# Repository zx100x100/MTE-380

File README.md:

# MTE-380
Repo for all mechanical, electrical and software designs for our MTE-380 Robot

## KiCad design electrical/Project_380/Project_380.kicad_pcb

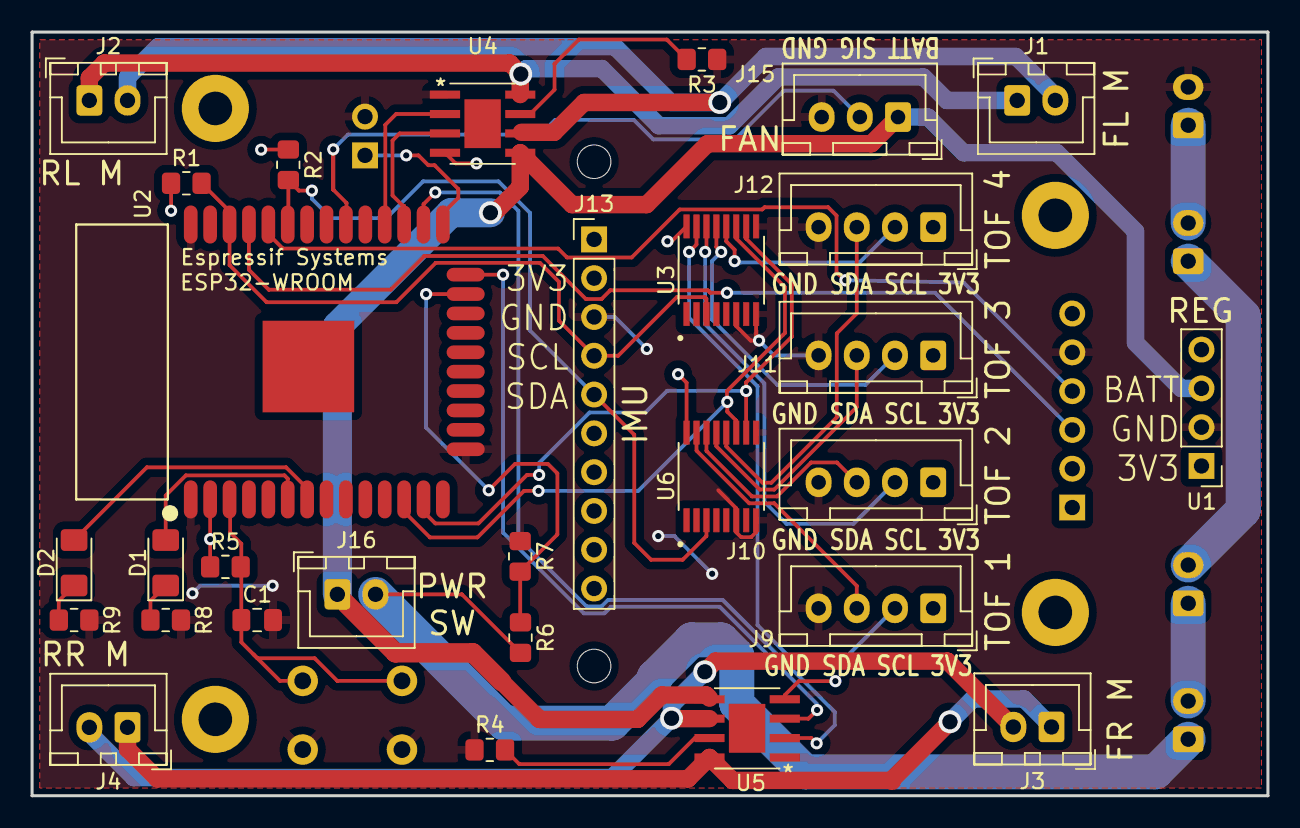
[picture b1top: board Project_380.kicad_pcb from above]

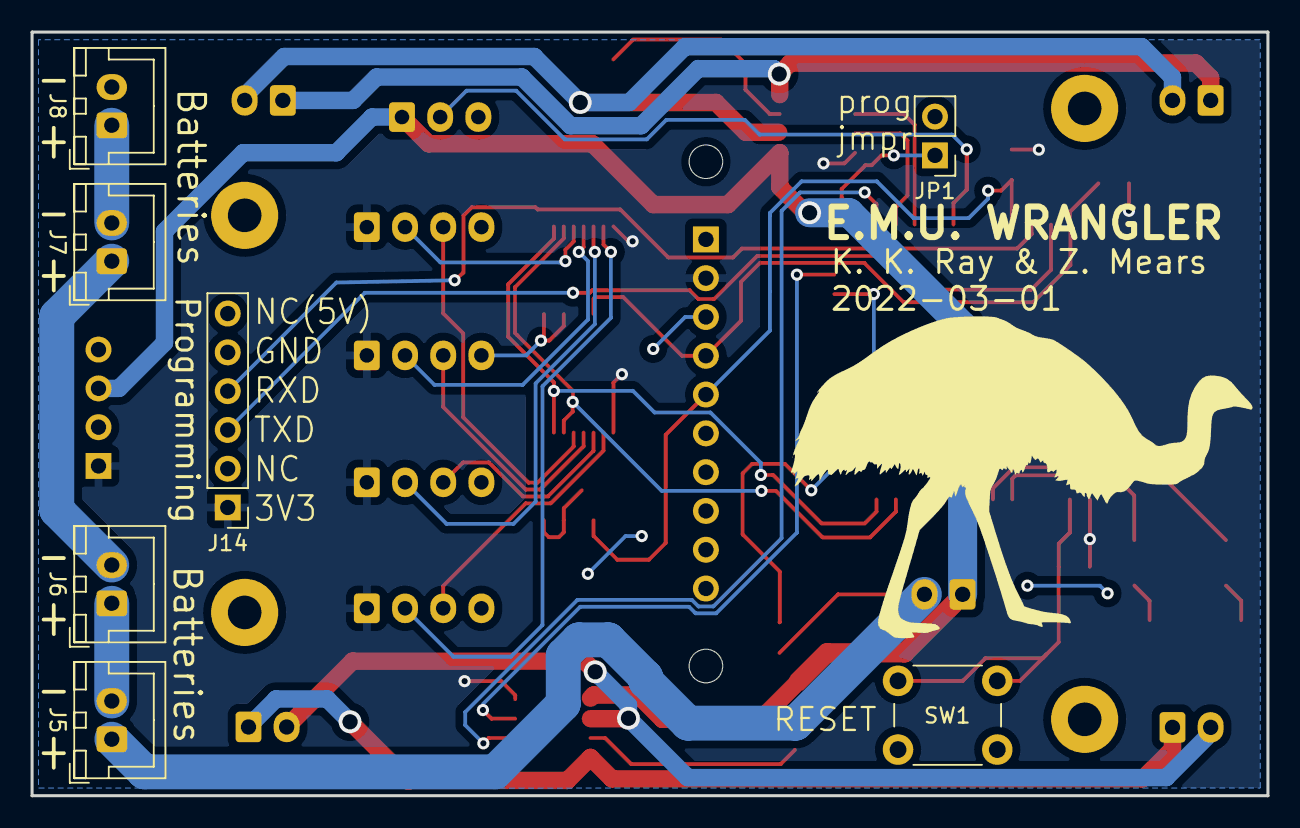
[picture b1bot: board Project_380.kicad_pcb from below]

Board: 2 copper layers, 80.9 x 50.0 mm, 36 parts (7 on the bottom side), 39 nets.

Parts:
C1: 0.1uF; C_0805_2012Metric_Pad1.18x1.45mm_HandSolder
D1, D2: LED; LED_1206_3216Metric_Pad1.42x1.75mm_HandSolder
J1: FL_Motor; JST_XH_B2B-XH-A_1x02_P2.50mm_Vertical
J2: RL_Motor; JST_XH_B2B-XH-A_1x02_P2.50mm_Vertical
J3: FR_Motor; JST_XH_B2B-XH-A_1x02_P2.50mm_Vertical
J4: RR_Motor; JST_XH_B2B-XH-A_1x02_P2.50mm_Vertical
J5, J6, J7, J8: Battery; JST_XH_B2B-XH-A_1x02_P2.50mm_Vertical
J9: ToF 1; JST_XH_B4B-XH-A_1x04_P2.50mm_Vertical
J10: ToF 2; JST_XH_B4B-XH-A_1x04_P2.50mm_Vertical
J11: ToF 3; JST_XH_B4B-XH-A_1x04_P2.50mm_Vertical
J12: ToF 4; JST_XH_B4B-XH-A_1x04_P2.50mm_Vertical
J13: IMU; PinHeader_1x10_P2.54mm_Vertical
J14: UART_to_USB; PinHeader_1x06_P2.54mm_Vertical
J15: DWN_Motor; JST_XH_B3B-XH-A_1x03_P2.50mm_Vertical
J16: Switch; JST_XH_B2B-XH-A_1x02_P2.50mm_Vertical
JP1: Jumper; PinHeader_1x02_P2.54mm_Vertical
R1, R2: 4K7; R_0805_2012Metric_Pad1.20x1.40mm_HandSolder
R3, R4: 0R; R_0805_2012Metric_Pad1.20x1.40mm_HandSolder
R5, R7: 10K; R_0805_2012Metric_Pad1.20x1.40mm_HandSolder
R6: 56K; R_0805_2012Metric_Pad1.20x1.40mm_HandSolder
R8, R9: 120; R_0805_2012Metric_Pad1.20x1.40mm_HandSolder
SW1: SW_SPST; SW_PUSH_6mm_H4.3mm
U1: HW613; PinHeader_1x04_P2.54mm_Vertical
U2: ESP32-WROOM
U3, U6: NX3L4051PW,118; SOP65P640X110-16N
U4, U5: TB67H451FNG_EL

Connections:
+3V3: J9.1, J10.1, J11.1, J12.1, J13.2, J14.1, R1.1, R2.1, R5.1, U1.1, U2.2 (3V3), U3.16 (VCC), U4.4 (VREF), U5.4 (VREF), U6.16 (VCC)
+BATT: J15.1, J16.1, U1.3, U4.5 (VM), U5.5 (VM)
/Motor Control/DWN_MTR_CTL: J15.2, U2.30 (IO18)
/Motor Control/M_CTL_L1: U2.27 (IO16), U4.3 (IN1)
/Motor Control/M_CTL_L2: U2.28 (IO17), U4.2 (IN2)
/Motor Control/M_CTL_R1: U2.24 (IO2), U5.3 (IN1)
/Motor Control/M_CTL_R2: U2.26 (IO4), U5.2 (IN2)
/Power Supply/V_SENSE: R6.1, R7.2, U2.23 (IO15)
/SEL_1: U2.12 (IO27), U3.11 (S1), U6.11 (S1)
/SEL_2: U2.13 (IO14), U3.10 (S2), U6.10 (S2)
/Sensors/J9_SCL: J9.2, U3.15 (Y2)
/Sensors/J9_SDA: J9.3, U6.15 (Y2)
/Sensors/J10_SCL: J10.2, U3.14 (Y1)
/Sensors/J10_SDA: J10.3, U6.14 (Y1)
/Sensors/J11_SCL: J11.2, U3.13 (Y0)
/Sensors/J11_SDA: J11.3, U6.13 (Y0)
/Sensors/J12_SCL: J12.2, U3.12 (Y3)
/Sensors/J12_SDA: J12.3, U6.12 (Y3)
/Sensors/SCL: J13.4, R1.2, U2.36 (IO22), U3.3 (Z)
/Sensors/SDA: J13.5, R2.2, U2.33 (IO21), U6.3 (Z)
GND: C1.2, J8.2, J9.4, J10.4, J11.4, J12.4, J13.3, J14.5, J15.3, JP1.2 (B), R3.1, R4.1, R7.1, R8.2, R9.2, SW1.1 (A), U1.2, U2.1 (GND), U2.15 (GND), U2.38 (GND), U3.6 (~E), U3.8 (GND), U3.9 (S3), U4.1 (GND), U5.1 (GND), U6.6 (~E), U6.8 (GND), U6.9 (S3)
unnamed: C1.1, R5.2, SW1.2 (B), U2.3 (EN)
unnamed: D1.1 (K), R8.1
unnamed: D2.1 (K), R9.1
unnamed: J1.1, J2.1, U4.8 (OUT2)
unnamed: J1.2, J2.2, U4.6 (OUT1)
unnamed: J3.1, J4.1, U5.8 (OUT2)
unnamed: J3.2, J4.2, U5.6 (OUT1)
unnamed: J5.2, J6.1
unnamed: J6.2, J7.1
unnamed: J7.2, J8.1
unnamed: J14.3, U2.35 (TXD0)
unnamed: J14.4, U2.34 (RXD0)
unnamed: J5.1, J16.2, R6.2
unnamed: JP1.1 (A), U2.25 (IO0)
unnamed: R3.2, U4.7 (RS)
unnamed: R4.2, U5.7 (RS)
unnamed: D1.2 (A), U2.6 (IO34)
unnamed: D2.2 (A), U2.7 (IO35)

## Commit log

2022-01-22 Create initial commit with IMU driver support
2022-01-30 Add motor driver support
2022-02-01 Add code changes to support ESP32
2022-02-02 Created struct for position to be passed from navigation to guidance
2022-02-03 added electrical schematics
2022-02-03 added downforce motor control pin
2022-02-03 added reset functionality, created schematic pdfs
2022-02-21 Add currently useless code fragments that will form TOF codebase
2022-02-21 Add demo code for TOFs
2022-02-22 created protobuf definitions
2022-02-22 working TCP server + client
2022-02-22 Initial commit of navigation
2022-02-23 proto worky
2022-02-23 fix merge conflict
2022-02-23 fix more merge conflict
2022-02-23 remote deprecated TCP client
2022-02-23 temp, working remote decode
2022-02-24 kinda almost working?
2022-02-24 refactor compiles!
2022-02-24 added motor controller
2022-02-24 stuff compiles
2022-02-25 telememetry integration!
2022-02-25 a bunch of telemetry updates
2022-02-25 move deprecated version of navigation out
2022-02-26 last commit message before I start having to use real descriptions :(
2022-02-26 stuff
2022-02-26 remove print statements
2022-03-01 Init commit of test code for imu
2022-03-01 make dashboard multithreaded
2022-03-01 more dashboard stuff
2022-03-01 Add design FOR THE RIGHT DONE GOT DANG PeeCeeBee
2022-03-01 Make fixes to board, add silkscreen, and generate gerbers
2022-03-03 Add STEP file of PCB
2022-03-03 Fix drawing template
2022-03-03 Add drawing template
2022-03-03 Add wheel and motor drive assembly
2022-03-03 added screw, chassis drawing
2022-03-03 added baseplate, assembly, chassis
2022-03-03 Fix mounting hole spacing
2022-03-03 add shaft hub CAD
2022-03-03 Create initial commit of mech designs
2022-03-03 Add prototype wheel and chasis designs
2022-03-03 Design fan shroud and quarentine SW2021 models
2022-03-03 Add batteries and PCB CAD
2022-03-03 Add drawing for full assembly
2022-03-03 Adjust hole sizes and improve fan shroud
2022-03-03 Add PCB mounting holes
2022-03-04 add PCB Assembly
2022-03-04 stubs
2022-03-04 Add functional Hello World TOF code
2022-03-04 Integrated tof sample code
2022-03-04 generate network info from python
2022-03-04 fix tof thing
2022-03-04 git ignores
2022-03-04 remove stinky
2022-03-04 pls stop changing this nut man
2022-03-04 ahmads state is cool
2022-03-04 let x button kill dashboard
2022-03-05 add some broken traj stuff
2022-03-07 add seperate log levels
2022-03-07 general log levels and stability stuff
2022-03-07 Changed tof code to main and passing pointers.
2022-03-07 Increased output buffer size
2022-03-08 guidance and trap position marking
2022-03-08 resize readouts a bit
2022-03-08 make makefile for protobufs crossplatform
2022-03-08 mildly improve useability of makefile
2022-03-09 ahmad do stuff
2022-03-09 nutman stuff
2022-03-09 Nav compiles
2022-03-09 add sim mode
2022-03-09 disable broken guidance shit
2022-03-09 Put shit behind log levels
2022-03-09 some debug
2022-03-09 improve dashboard fault tolerance more
2022-03-09 more dashboard improvements to stability
2022-03-09 made tofs non blocking
2022-03-09 prevent trying to plot strings
2022-03-09 accounte for overflow in counter comparison
2022-03-09 Add new TOF mounts and suppress fan system
2022-03-09 start adding sim shit
2022-03-09 Attempted to make tof non blocking. (poorly)
2022-03-09 set clock speed, time some stuff
2022-03-10 traj
2022-03-10 some stubs
2022-03-14 Add updated baseplate
2022-03-14 add sim position, velocity, acceleration calculations
2022-03-14 make wifi code work a bit better
2022-03-15 Serial print udpates
2022-03-15 get sim stuff mostly worky
2022-03-15 temp
2022-03-15 Add updated schematic PDF
2022-03-15 fix vel setpoint indicators and other stuff
2022-03-15 fix some temp shit
2022-03-15 ensure robot only travels in direction it is facing
2022-03-15 fix some of it
2022-03-16 Add MK3 Wheel design
2022-03-17 slight network fix, improve sim
2022-03-17 improved error checking for tf
2022-03-18 improved error checking
2022-03-18 cleanup
2022-03-18 make sim default off
2022-03-18 Use new mux
2022-03-18 fix plotting
2022-03-19 sensor stuff idk
2022-03-19 auto switch networks (linux only sorry not sorry)
2022-03-19 dashboard improvements
2022-03-19 Now using angle from wall
2022-03-19 updated tof testing and validation
2022-03-20 Updated tof code to use shutdown pin
2022-03-20 Changed from mm to ft
2022-03-21 merging with new nav stuff
2022-03-21 nav kinda works. no imu.
2022-03-21 ready for sensors??
2022-03-22 give heading pls
2022-03-22 ASFJIOSJIOAFJIOASJIOJIAFJILA
2022-03-22 remove bullshit
2022-03-22 make telemetry toggleable, add recording indicator, cleanup networking a bit
2022-03-22 get rid of deprecated errorInfo string
2022-03-23 stuff for my stuff
2022-03-23 make traj
2022-03-23 tof worky?
2022-03-23 lol prootos
2022-03-23 cleanup stuff
2022-03-23 more cleanup
2022-03-23 messed with kalman filter
2022-03-23 fix variable
2022-03-23 Tidy up a few pieces of the code base
2022-03-23 tof test now muxes through all of them
2022-03-23 Add a few coments and tidy a bit
2022-03-23 cleanup and add turn_in_place_test
2022-03-23 add DT multipliers back in
2022-03-23 turnonspot code
2022-03-23 turn in place worky
2022-03-23 hopefully handle bad values in plots?
2022-03-23 fix numbers better
2022-03-23 temp prints
2022-03-23 fix print
2022-03-23 made 'improvements' to tof driver api thingy
2022-03-23 more error checking dashboard
2022-03-23 made tof re-init things
2022-03-23 fix thing for Z money in the house
2022-03-23 flash LEDs
2022-03-24 update teleop voltage, sleep, defaul logger level
2022-03-24 Add some coments and things
2022-03-24 Add ability to set motor PWM frequency
2022-03-24 do not use mux for tof
2022-03-24 made test code only for 2 independednt tofs, no mux
2022-03-24 Add non-functional minor fixes to new TOF init
2022-03-25 Fix code for new TOF electrical configuration
2022-03-25 recording semi working
2022-03-25 resolve more merge conflict
2022-03-25 stuff2
2022-03-25 check for consecutive bad readings, reset if high
2022-03-25 get rid of nav early return (temp)
2022-03-25 Minor changes to TOF rebooting
2022-03-25 Port TOF library to our codebase, and make minor changes
2022-03-25 more nav checks are cool
2022-03-25 Uncomment the re-inits
2022-03-25 motor power print statements
2022-03-25 made it constant velocity instead of constant acceleration
2022-03-25 add heading to guidancedata
2022-03-25 added left front and angFromWall to nav proto
2022-03-25 fix thing
2022-03-26 some guidance
2022-03-26 now taking the best guess between front and back. also fixed bracket error in back estimate. also made funny pun
2022-03-26 nav kinda boppin rn
2022-03-26 just changed gain values
2022-03-26 playback shit
2022-03-26 message delimit more carefully, still fails wtf
2022-03-26 fix bad data reading problem
2022-03-27 shit working slowly + nav eventually shits itself
2022-03-27 fix nav n shit
2022-03-28 sorry
2022-03-28 refactor
2022-03-29 CAD finalized for carbon fiber chasis
2022-03-29 more sorry
2022-03-29 fixed bad variable
2022-03-29 made tof thread test
2022-03-29 added broken tof thread test code
2022-03-29 Made red LED as indicator for updateWallAngleAndDistance
2022-03-29 assuming this code works per K's advice
2022-03-29 breaking for motors
2022-03-29 more tof threading fuckery
2022-03-29 move files around idk
2022-03-29 add mutexes
2022-03-30 mutex debugging
2022-03-30 some stuff that helped a bit?
2022-03-30 demo-code-multithread-1tof-works-on-robot i swear
2022-03-30 demo-code-multithread-4tof-works-on-robot
2022-03-30 put watchdog in a seperate thread
2022-03-30 multithreading 90% working but also this proves we dont need it. be careful, robot DRIVES
2022-03-31 weds night
2022-03-31 tune slow mode
2022-03-31 megaslow
2022-04-01 working!!!!!!!!!!!!!! ish
2022-04-01 IMG_0263
2022-04-01 distractions
2022-04-01 wiggly but slew rate fixed on motor AND on drive PID
2022-04-01 before adding stops at the last few turnys
2022-04-01 worky ish
2022-04-01 blahhhhhhhhhhh good stuff guys i love
2022-04-01 WORKING RUN
2022-04-01 minor corrections
2022-04-01 final adjustment
2022-04-01 most consistent yet
2022-04-01 fast working

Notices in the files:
parts and their libraries:
Copyright 2021 Accelerated Designs. All rights reserved.
